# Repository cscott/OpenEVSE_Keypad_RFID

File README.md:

# OpenEVSE Capacitive keypad and RFID reader

Thing tracker at
https://cscott.github.io/thing-tracker/#/thing/c6539aa6-b8c7-4adf-a22c-1baba5bbef97

There is a [Hackaday page for this project].

Discussion in the OpenEVSE forum at
https://openev.freshdesk.com/support/discussions/topics/6000067515

## Description

This repository contains hardware design files for a capacitive
keypad and RFID reader for [OpenEVSE] hardware.

More details can be found on the
[Hackaday page for this project].

<br clear="both" />

## Instructions

### Step 1: Purchase components

You will need to purchase a new
[Polycase ML-58 enclosure](https://www.polycase.com/ml-58f), although
the only part we will need from it is the clear front cover.  (Perhaps
we can arrange a special purchase of just the cover if demand
warrants.)

You will also need to purchase or have the Keypad PCB fabricated.  The
KiCad design files are in the [`Keypad-Front`](./Keypad-Front)
subdirectory. It's a four-layer PCB, and I recommend white silkscreen
to avoid heating when in direct sun.  I used 1oz copper on a standard
1.6mm thick PCB.  I found that [JLCPCB](https://jlcpcb.com/) had
very reasonable prices.

I assume you also own an
[OpenEVSE Advanced Series](https://store.openevse.com/collections/all-products)
and have assembled it.

You will also need an LCD mount, which can be 3d printed.  You *might*
be able to reuse the one from your existing OpenEVSE device, but
you'll need to pry the glue off then cut down the top bar. It's
probably easier just to print a new one.

[`lcd-trim-more.stl`]

For compatibility with the latest OpenEVSE web interface, you will
also need to update the firmware on your main OpenEVSE controller
board.  This is out of scope for this guide, but you can find
instructions HERE.  It's a good thing to do between step 3 and 4
when you have your OpenEVSE charger disconnected and open.

### Step 2: Purchase or fabricate I2C cable

You will also need an I2C cable from the OpenEVSE Wifi board.  If you
have the latest-generation WiFi board, this will be a STEMMA-QT cable
(JST-SH, with 1.0mm pitch).  Older boards had an 8-pin JST-PH
connector (2.0mm pitch) and you will have to fabricate an adapter
yourself.

TODO: photos here

### Step 3: Remove cover from OpenEVSE

Unplug your OpenEVSE.  Don't try to do this with your OpenEVSE still
connected to mains power!

Remove the old printed blue cover from your OpenEVSE.  Disconnect
the cable leading from the OpenEVSE main board to the LCD display.

TODO: photo here.

### Step 4: Move the LCD module

Unscrew the LCD module from your old device and screw it onto the new
LCD mount.  You will then need to attach the new LCD mount to the
Keypad PCB, using the silkscreen as a guide.  I found that hot glue
worked well, but other adhesives are probably fine as well.

TODO: photo here

### Step 5: Mount the new PCB

You will now attach the Keypad PCB to the inside of your new clear
ML-58 enclosure cover.  I found that placing the board inside
the cover and then using generous drops of hot glue around the
screw bosses secured the Keypad PCB in a reversible manner, so that I
could still remove it if I needed to later.

TODO: photo here

If you're braver, a clear contact-sensitive adhesive tape (3M
makes a number of different types) would make a more permanent
bond.  Eliminating the air gap between the front cover and the
Keypad PCB is said to yield better performance from capacitive touch
sensors, but the hot-glue method has worked well enough for me.

### Step 5: Connect cables

You will need to connect two cables:

1. The LCD cable that you removed in step 3.

TODO: photo here

2. The I2C cable from step 2, from the OpenEVSE Wifi board to the
STEMMA-QT-compatible ports on the Keypad PCB.

TODO: photo here

### Step 6: Reattach the cover

Screw the cover back on the OpenEVSE!

TODO: photo here

### Step 7: Update OpenEVSE firmware

You'll need to reflash the OpenEVSE to the latest firmware.  The
good news is that you can do this over the web interface!

TODO: instructions here

### Step 8: Add some PINs and cards

TODO: instructions here

### Step 9: Optional improvements

The Keypad PCB also contains an MCP9808 temperature sensor and pads
for a DS3231MZ real-time clock.  Some older versions of the OpenEVSE
hardware contained an MCP9808 daisy-chained from the LCD module and
secured to the front cover.  If your hardware is like this, then
you can use the MCP9808 on the board by connecting the LCD display
to this port on the keypad PCB:

TODO: photo here

You should be able to use your existing cable, but if you have to
purchase or fabricate a new one, it's a STEMMA-QT compatible JST-SH
(1.0mm pitch) on the Keypad PCB side.  On my example, it was JST-PH
(2.0mm pitch) on the LCD side, and you can [buy an appropriate cable
from Adafruit](https://www.adafruit.com/product/4424).

Similarly, *newer* versions of the OpenEVSE hardware omit the
real-time clock which was present on the original OpenEVSE LCD modules.
The justification is that, with ubiquitous network connectivity,
you don't need to pay the steep price (~$10) for a clock chip when
instead you can just ask the network what time it is.

However, if you have intermittent network connectivity at your
installation site, you might want the peace of mind of knowing that
your usage timestamps will always be correct.  Because the RTC chip
is not cheap, it is not populated on the keypad PCB by default,
although all of its support components are present.  You can buy
an appropriate chip ([Digikey part link](https://www.digikey.com/en/products/detail/analog-devices-inc-maxim-integrated/DS3231MZ/2754396))
and battery connector ([Digikey part link](https://www.digikey.com/en/products/detail/mpd-memory-protection-devices/BC-2003-TR/5027929))
and hand-solder them onto the footprints provided.  While you've got
the soldering iron hot, you will most likely want to *remove* the
MCP9808 chip present on the Keypad PCB, since as far as I'm aware
all of the LCD modules *missing* the RTC *also* have the MCP9808
already present on the LCD board.  You don't want two MCP9808s trying
to talk on the same I2C bus.

After adding the RTC, you'd connect the I2C cable from the LCD
module to the Keypad PCB just as done for the MCP9808 above.

## Related

* [OpenEVSE] project
* [Hackaday page for this project]

## License

These designs are licensed under the [CC-BY-SA-4.0] like the original
OpenEVSE designs.

[OpenEVSE]: https://www.openevse.com/
[Hackaday page for this project]: https://hackaday.io/project/194656-openevse-capacitive-keypad-rfid
[`lcd-trim-more.stl`]: ./lcd-trim-more.stl
[CC-BY-SA-4.0]: https://spdx.org/licenses/CC-BY-SA-4.0.html

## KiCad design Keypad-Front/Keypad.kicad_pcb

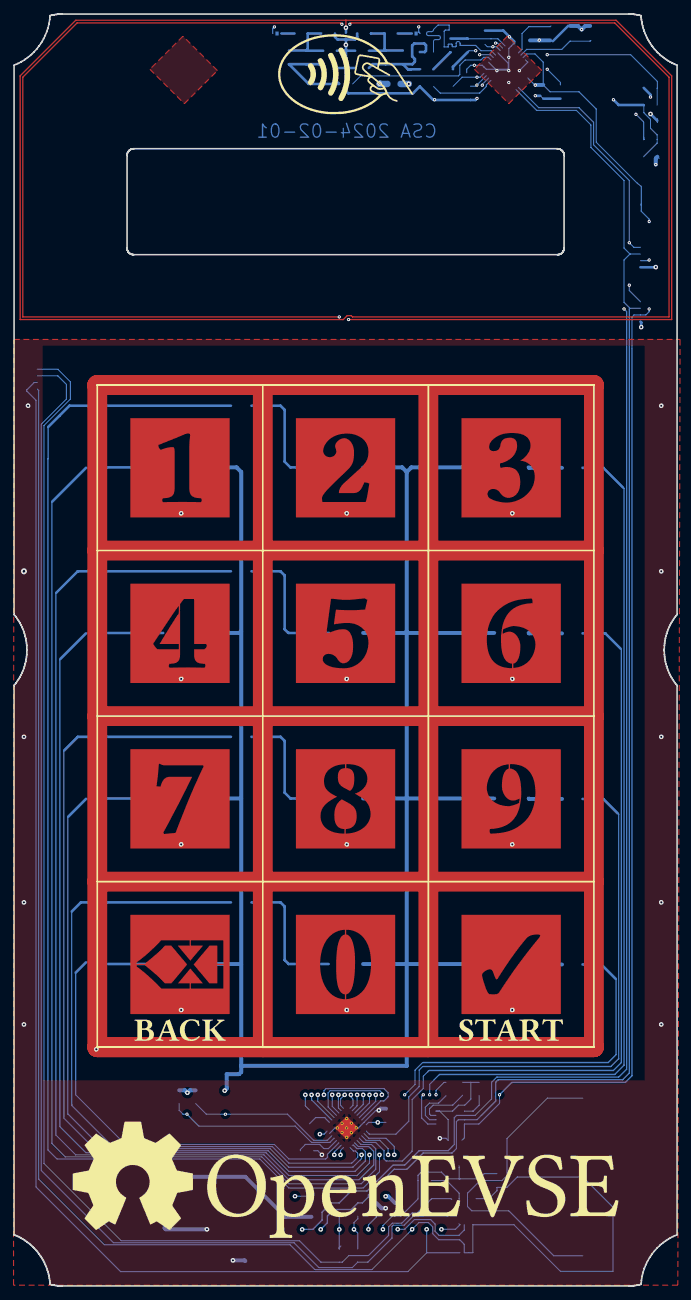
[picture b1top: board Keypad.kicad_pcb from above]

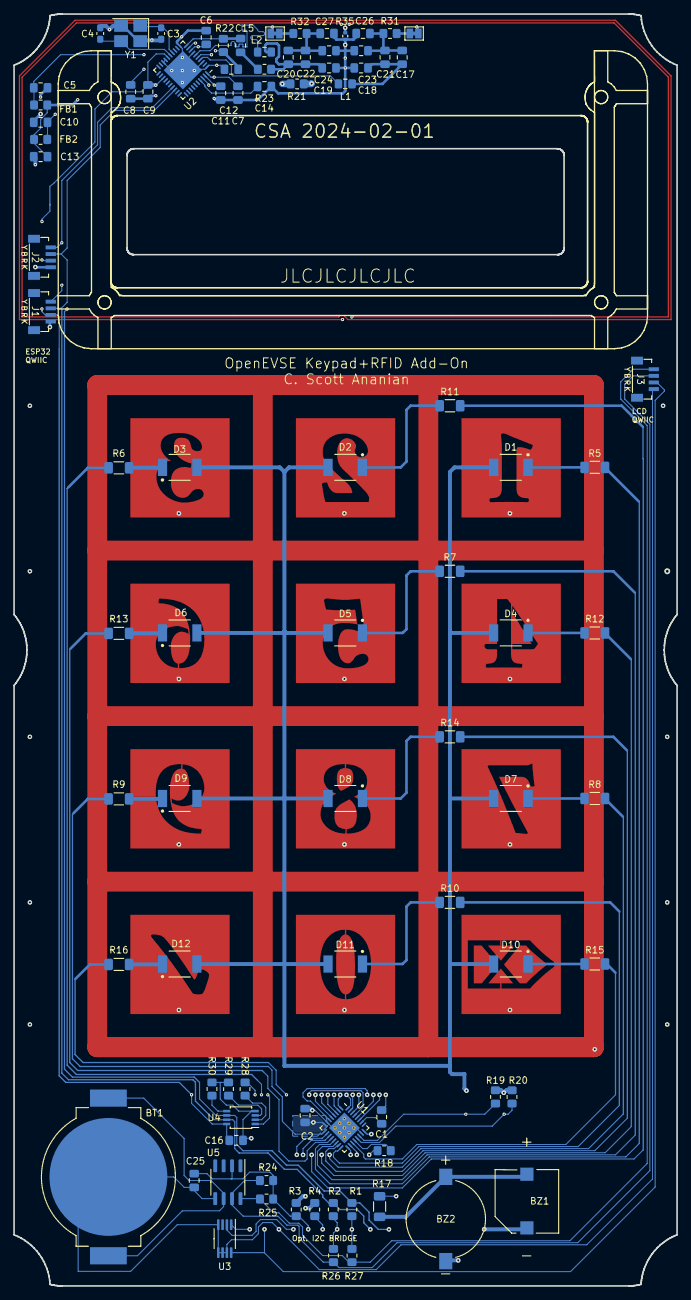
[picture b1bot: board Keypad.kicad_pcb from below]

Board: 4 copper layers, 100.1 x 192.1 mm, 103 parts (90 on the bottom side), 74 nets.

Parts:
BT1: CR2032; BatteryHolder_MPD_BC2003_1x2032
BZ1: FUET-9650B-3V
BZ2: PUI SMT-1220-TW-R; XDCR_SMT-1220-TW-R
C1: 47pF; C_0805_2012Metric_Pad1.18x1.45mm_HandSolder
C2, C6, C7, C8, C9, C11, C12, C13, C16, C25: .1uF; C_0805_2012Metric_Pad1.18x1.45mm_HandSolder
C3, C4: 33pF; C_0603_1608Metric_Pad1.08x0.95mm_HandSolder
C5, C10, C14: 10uF; C_0805_2012Metric_Pad1.18x1.45mm_HandSolder
C15: 1000pF; C_0805_2012Metric_Pad1.18x1.45mm_HandSolder
C17, C20, C26, C27: N/C; C_0805_2012Metric_Pad1.18x1.45mm_HandSolder
C18, C19: 220pF; C_0805_2012Metric_Pad1.18x1.45mm_HandSolder
C21, C22: 22pF; C_0805_2012Metric_Pad1.18x1.45mm_HandSolder
C23, C24: 100pF; C_0805_2012Metric_Pad1.18x1.45mm_HandSolder
D1, D2, D3, D4, D5, D6, D7, D8, D9, D10, D11, D12: SunLED XZVG45WT-9; SunLED_3.2x2.8mm_ReverseMount
FB1, FB2: Laird MI0805J102R-10; R_0805_2012Metric_Pad1.20x1.40mm_HandSolder
J1: EXP QWIIC; JST-SH-4-VERT-SMD
J2: TOUCH QWIIC; JST-SH-4-VERT-SMD
J3: RTC STEMMA QT; JST-SH-4-VERT-SMD
L1, L2: 560nH; L_0805_2012Metric_Pad1.15x1.40mm_HandSolder
R1, R2, R3, R4, R26, R27: 0; R_0805_2012Metric_Pad1.20x1.40mm_HandSolder
R5, R6, R7, R8, R9, R10, R11, R12, R13, R14, R15, R16, R17: 100; R_1206_3216Metric_Pad1.30x1.75mm_HandSolder
R18, R24, R25: 4.7k; R_0805_2012Metric_Pad1.20x1.40mm_HandSolder
R19, R20, R21: 10k; R_0805_2012Metric_Pad1.20x1.40mm_HandSolder
R22, R28, R29, R30: 1k; R_0805_2012Metric_Pad1.20x1.40mm_HandSolder
R23: 2.7k; R_0805_2012Metric_Pad1.20x1.40mm_HandSolder
R31, R32: 1.5; R_0805_2012Metric_Pad1.20x1.40mm_HandSolder
R33, R34: N/C; SolderJumper-2_P1.3mm_Bridged_Pad1.0x1.5mm
R35: 0; R_0402_1005Metric
TP1: Guard; Touch_Pad_D1.0mm
TP2: KEY 4; Touch_Pad_D1.0mm
TP3: KEY 7; Touch_Pad_D1.0mm
TP4: KEY 6; Touch_Pad_D1.0mm
TP5: KEY 1; Touch_Pad_D1.0mm
TP6: KEY 5; Touch_Pad_D1.0mm
TP7: KEY 8; Touch_Pad_D1.0mm
TP8: KEY 0; Touch_Pad_D1.0mm
TP9: KEY 2; Touch_Pad_D1.0mm
TP10: KEY 3; Touch_Pad_D1.0mm
TP11: KEY ENTER; Touch_Pad_D1.0mm
TP12: KEY 9; Touch_Pad_D1.0mm
TP13: KEY BACK; Touch_Pad_D1.0mm
U1: CAP1214; QFN-32-1EP_5x5mm_P0.5mm_EP3.3x3.3mm_ThermalVias
U2: PN5321A3HN_C1xx; HVQFN-40-1EP_6x6mm_P0.5mm_EP4.1x4.1mm
U3: MCP9808_MSOP; MSOP-8_3x3mm_P0.65mm
U4: PCA9536DP; TSSOP-8_3x3mm_P0.65mm
U5: DS3231MZ; SOIC-8_3.9x4.9mm_P1.27mm
Y1: 27.12MHz; Crystal_SMD_TXC_7M-4Pin_3.2x2.5mm_HandSoldering

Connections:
+3.3V: C2.1, C7.1, C9.1, C16.1, D1.2 (A), D2.2 (A), D3.2 (A), D4.2 (A), D5.2 (A), D6.2 (A), D7.2 (A), D8.2 (A), D9.2 (A), D10.2 (A), D11.2 (A), D12.2 (A), J1.2, J2.2, R3.1, R19.1, R20.1, R21.1, R28.2, U1.8 (VDD), U2.16 (I0), U2.23 (PVDD), U2.40 (VBAT), U4.8 (VDD)
+5V: C25.1, J3.2, R3.2, R24.1, R25.1, U3.8 (V_{DD}), U5.2 (VCC)
/FEEDBACK: BZ1.1 (+), BZ2.1 (+), R17.1
/FEED_N: C19.2, C20.1, C22.1, L2.2, R23.1
/FEED_P: C17.2, C18.1, C21.2, L1.2
/LED1: R5.1, U1.13 (LED5)
/LED2: R11.1, U1.17 (LED9)
/LED3: R6.1, U1.18 (LED10)
/LED4: R12.1, U1.10 (LED2)
/LED5: R7.1, U1.14 (LED6)
/LED6: R13.1, U1.12 (LED4)
/LED7: R8.1, U1.11 (LED3)
/LED8: R14.1, U1.15 (LED7)
/LED9: R9.1, U1.9 (LED1)
/LED10: R15.1, U1.19 (LED11)
/LED11: R10.1, U1.16 (LED8)
/LED12: R16.1, U4.1 (IO0)
/RTC_SCL: J3.4, R25.2, R27.1, U5.8 (SCL)
/RTC_SDA: J3.3, R24.2, R26.1, U5.7 (SDA)
/TEMP_SCL: R1.2, R27.2, U3.2 (SCL)
/TEMP_SDA: R2.2, R26.2, U3.1 (SDA)
/TOUCH_1: TP5.1, U1.30 (CS5)
/TOUCH_2: TP9.1, U1.2 (CS9)
/TOUCH_3: TP10.1, U1.3 (CS10)
/TOUCH_4: TP2.1, U1.27 (CS2)
/TOUCH_5: TP6.1, U1.31 (CS6)
/TOUCH_6: TP4.1, U1.29 (CS4)
/TOUCH_7: TP3.1, U1.28 (CS3)
/TOUCH_8: TP7.1, U1.32 (CS7)
/TOUCH_9: TP12.1, U1.5 (CS12)
/TOUCH_10: TP13.1, U1.6 (CS13)
/TOUCH_11: TP8.1, U1.1 (CS8)
/TOUCH_12: TP11.1, U1.4 (CS11)
/TOUCH_GUARD: C1.1, TP1.1
/TOUCH_SCL: J1.4, J2.4, R1.1, R19.2, U1.22 (SMCLK), U2.27 (NSS/P50_SCL/HSU_RX), U4.6 (SCL)
/TOUCH_SDA: J1.3, J2.3, R2.1, R20.2, U1.21 (SMDATA), U2.28 (MOSI/SDA/HSU_TX), U4.7 (SDA)
/TX_N: L2.1, U2.6 (TX2)
/TX_P: L1.1, U2.4 (TX1)
GND1: BZ1.2 (-), BZ2.2 (-), C2.2, C3.1, C4.1, C5.2, C6.1, C7.2, C8.1, C9.2, C10.2, C11.2, C12.2, C13.1, C14.2, C16.2, C18.2, C19.1, C23.2, C24.1, C26.2, C27.1, J1.1, J2.1, R4.1, R18.2, R29.2, R30.2, R35.1, U1.7 (CS14), U1.23 (RESET), U1.33 (GND), U2.1 (DVSS), U2.3 (TVSS1), U2.7 (TVSS2), U2.11 (AVSS), U2.17 (I1), U2.18 (TESTEN), U2.41 (AVSS), U4.4 (VSS), Y1.2, Y1.4
GND2: BT1.2 (-), C25.2, J3.1, R4.2, U3.4 (GND), U3.5 (A2), U3.6 (A1), U3.7 (A0), U5.5 (GND)
unnamed: BT1.1 (+), U5.6 (VBAT)
unnamed: C15.2, R23.2
unnamed: C17.1, C21.1, C23.1, C26.1, R31.2
unnamed: C20.2, C22.2, C24.2, C27.2, R32.1
unnamed: D1.1 (K), R5.2
unnamed: D2.1 (K), R11.2
unnamed: D3.1 (K), R6.2
unnamed: D4.1 (K), R12.2
unnamed: D5.1 (K), R7.2
unnamed: D6.1 (K), R13.2
unnamed: D7.1 (K), R8.2
unnamed: D8.1 (K), R14.2
unnamed: D9.1 (K), R9.2
unnamed: D10.1 (K), R15.2
unnamed: D11.1 (K), R10.2
unnamed: D12.1 (K), R16.2
unnamed: R31.1, R33.2
unnamed: R32.2, R34.1
unnamed: R33.1, R34.2, R35.2
unnamed: R18.1, U1.20 (ALERT)
unnamed: C1.2, U1.26 (CS1)
unnamed: R17.2, U1.24 (FEEDBACK)
unnamed: C5.1, C6.2, FB1.2, U2.8 (AVDD)
unnamed: C3.2, U2.14 (OSCIN), Y1.1
unnamed: C4.2, U2.15 (OSCOUT), Y1.3
unnamed: C15.1, R22.2, U2.10 (RX)
unnamed: C14.1, U2.37 (SVDD)
unnamed: C8.2, C10.1, FB2.2, U2.5 (TVDD)
unnamed: C12.1, R22.1, U2.9 (VMID)
unnamed: R21.2, U2.38 (~RSTPD)
unnamed: R28.1, U4.2 (IO1)
unnamed: R29.1, U4.3 (IO2)
unnamed: R30.1, U4.5 (IO3)
VCC: C11.1, C13.2, FB1.1, FB2.1, U2.39 (DVDD)

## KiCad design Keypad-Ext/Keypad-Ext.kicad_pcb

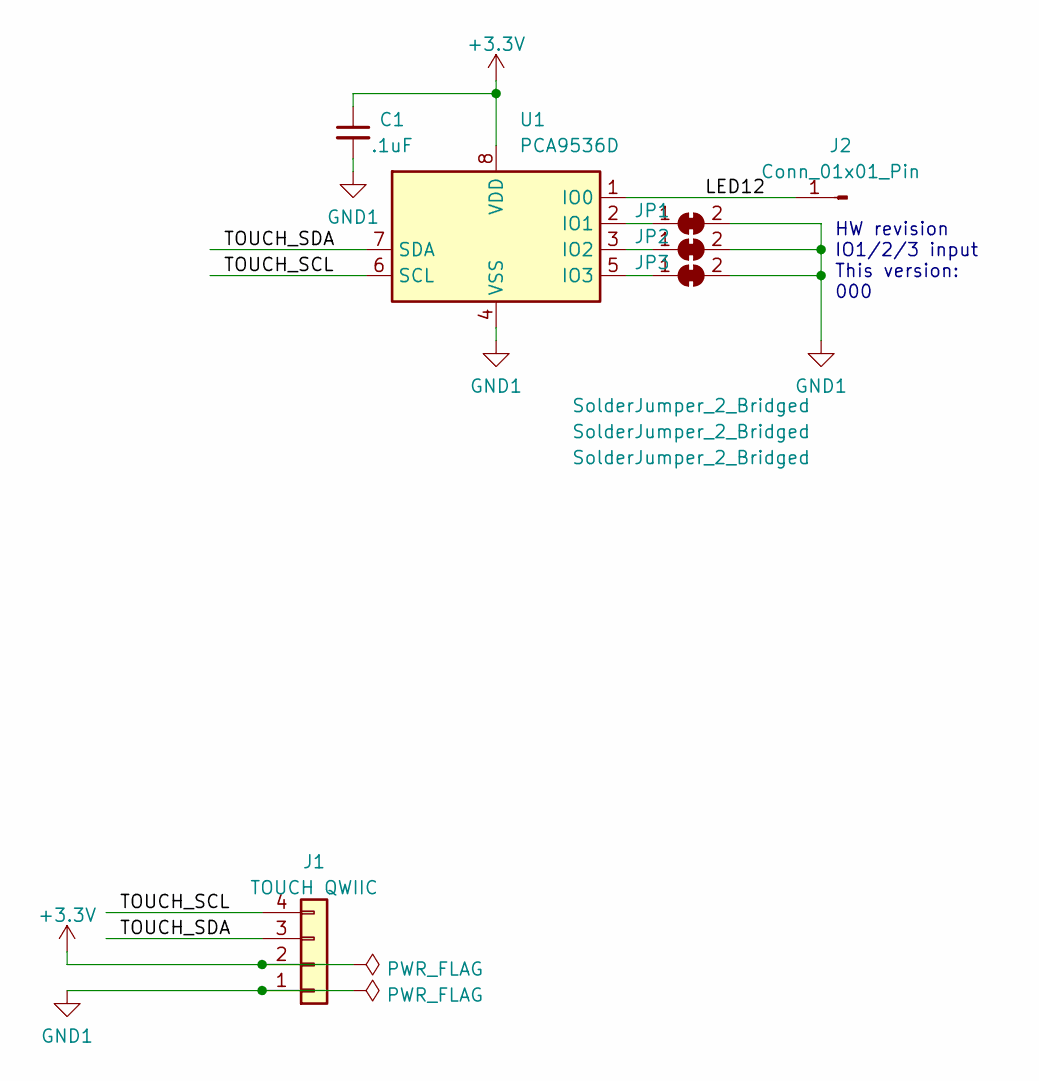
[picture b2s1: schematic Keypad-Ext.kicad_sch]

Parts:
C1: .1uF; C_0805_2012Metric_Pad1.18x1.45mm_HandSolder; LCSC C138340
J1: TOUCH QWIIC; JST-SH-4-VERT-SMD; LCSC C160390
J2: Conn_01x01_Pin; PinHeader_1x01_P2.54mm_Vertical
JP1, JP2, JP3: SolderJumper_2_Bridged; SolderJumper-2_P1.3mm_Bridged_Pad1.0x1.5mm
U1: PCA9536D; SOIC-8_3.9x4.9mm_P1.27mm; LCSC C2688883

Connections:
+3.3V: C1.1, J1.2, U1.8 (VDD)
/LED12: J2.1, U1.1 (IO0)
/TOUCH_SCL: J1.4, U1.6 (SCL)
/TOUCH_SDA: J1.3, U1.7 (SDA)
GND1: C1.2, J1.1, JP1.2 (B), JP2.2 (B), JP3.2 (B), U1.4 (VSS)
unnamed: JP1.1 (A), U1.2 (IO1)
unnamed: JP2.1 (A), U1.3 (IO2)
unnamed: JP3.1 (A), U1.5 (IO3)

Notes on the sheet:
HW revision IO1/2/3 input This version: 000

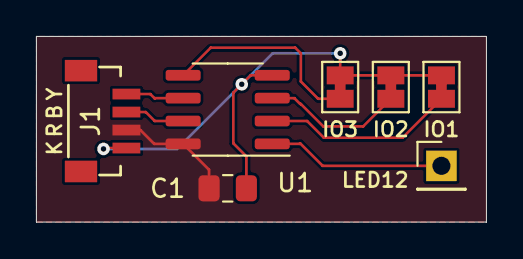
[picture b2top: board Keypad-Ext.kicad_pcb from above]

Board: 2 copper layers, 25.0 x 10.3 mm, 7 parts (0 on the bottom side), 8 nets.

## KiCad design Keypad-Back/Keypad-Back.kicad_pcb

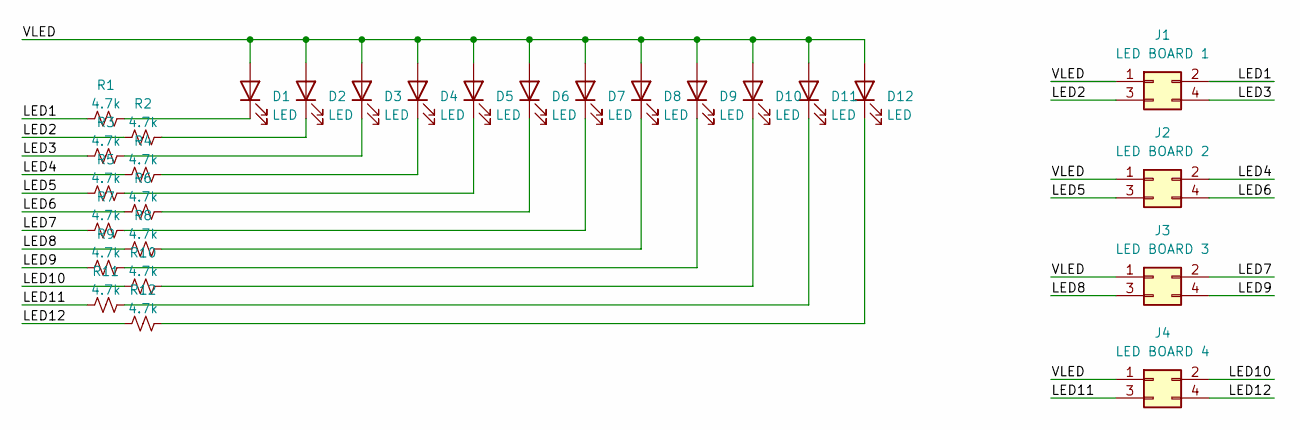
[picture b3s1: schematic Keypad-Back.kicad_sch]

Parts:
D1, D2, D3, D4, D5, D6, D7, D8, D9, D10, D11, D12: LED; LED_1206_3216Metric_Pad1.42x1.75mm_HandSolder
J1: LED BOARD 1; PinHeader_2x02_P2.54mm_Vertical_SMD
J2: LED BOARD 2; PinHeader_2x02_P2.54mm_Vertical_SMD
J3: LED BOARD 3; PinHeader_2x02_P2.54mm_Vertical_SMD
J4: LED BOARD 4; PinHeader_2x02_P2.54mm_Vertical_SMD
R1, R2, R3, R4, R5, R6, R7, R8, R9, R10, R11, R12: 4.7k; R_0805_2012Metric_Pad1.20x1.40mm_HandSolder

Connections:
/LED1: J1.2, R1.1
/LED2: J1.3, R2.1
/LED3: J1.4, R3.1
/LED4: J2.2, R4.1
/LED5: J2.3, R5.1
/LED6: J2.4, R6.1
/LED7: J3.2, R7.1
/LED8: J3.3, R8.1
/LED9: J3.4, R9.1
/LED10: J4.2, R10.1
/LED11: J4.3, R11.1
/LED12: J4.4, R12.1
/VLED: D1.2 (A), D2.2 (A), D3.2 (A), D4.2 (A), D5.2 (A), D6.2 (A), D7.2 (A), D8.2 (A), D9.2 (A), D10.2 (A), D11.2 (A), D12.2 (A), J1.1, J2.1, J3.1, J4.1
unnamed: D1.1 (K), R1.2
unnamed: D2.1 (K), R2.2
unnamed: D3.1 (K), R3.2
unnamed: D4.1 (K), R4.2
unnamed: D5.1 (K), R5.2
unnamed: D6.1 (K), R6.2
unnamed: D7.1 (K), R7.2
unnamed: D8.1 (K), R8.2
unnamed: D9.1 (K), R9.2
unnamed: D10.1 (K), R10.2
unnamed: D11.1 (K), R11.2
unnamed: D12.1 (K), R12.2

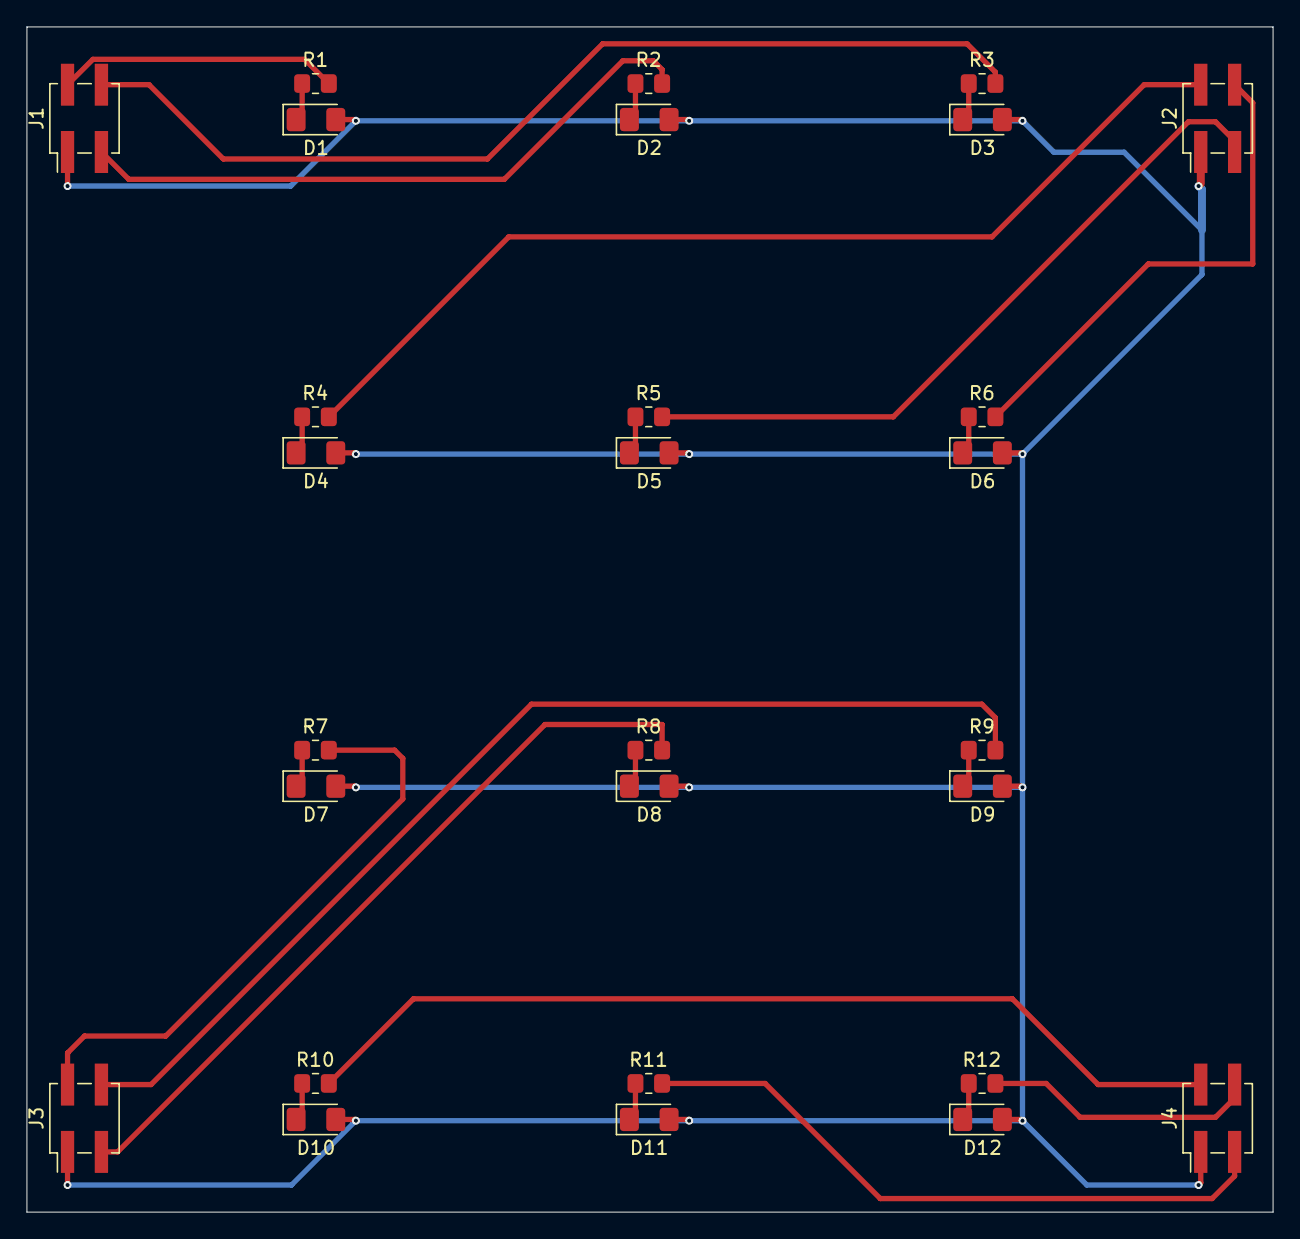
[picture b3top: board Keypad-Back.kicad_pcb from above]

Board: 2 copper layers, 93.5 x 88.9 mm, 28 parts (0 on the bottom side), 25 nets.

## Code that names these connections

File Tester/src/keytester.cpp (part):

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    cap1214_write(CAP1214_REG_SENSOR_LED_LINKING, 0x76);
  }
  // LED/GPIO pins are outputs!
  cap1214_write(CAP1214_REG_LED_GPIO_DIRECTION, 0xFF); // LED1-LED8 = output
  // flip polarity of all LEDs (normally off, to keep power low)
  polarity = POLARITY_ASLEEP;
  cap1214_write(CAP1214_REG_LED_POLARITY_1, polarity);
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  if (st3 & 0xF) { merged |= 0x80; }

#define merged_cs(x) (merged & (((uint16_t)1)<<(x-1)))
  // manually set feedback pins for CS8-CS13
  // CS8/9/10 -> LED8/9/10
  uint8_t led1 = 0, led2 = 0, led3 = 0;
  static bool saw_cs8 = false;
  if (merged_cs(8)) { // CS8 (touch 11, key 0)
    led1 |= 0x80;
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
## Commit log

2023-07-04 Initial version of OpenEVSE keypad
2023-07-04 Reorg into separate front and back PCB
    This would allow the use of "normal" front-view LEDs, ie UV LEDs
    to exploit the "natural" flourescence of FR4.
2023-07-05 Back to a one-board design with rear-firing LEDs
    Giving up on the UV LED idea for now.
2023-07-05 Steady work on Keypad PCB
2023-07-06 Attempt 2 at routing, cap sensor at bottom
2023-07-07 Take 3, the JST-XH for the feedback is too large.
2023-07-08 Complete!
2023-07-08 First version of gerbers
2023-07-09 Second version, to fix the disconnected touch pad centers
    Tried to get JLCPCB to adopt this, but apparently unsuccessfully.
2023-07-10 Third version, no vias to cast shadows.
    Also add the BOM.
2023-09-04 Keypad tester skeleton
2023-09-06 Fix schematic and PCB
    1. Swap LED6 and LED11 so that the dual LED is on the high-power port.
    (This change isn't green-wired on the existing boards.)
    2. Add 47pF series cap to TOUCH_GUARD to bring it into spec.
    (Measured at 80pF; CAP1214 supports 50pF max.)
    3. Fix RESET -- it should be grounded, not tied high.
2023-09-06 First complete key tester
2023-09-06 Tweak sensitivity and other values
2023-09-06 More tweaks & testing of proximity feature
2023-09-06 Improve key press responsiveness
2023-09-07 Fix handling of zero key (CS8) which has a weird press-and-hold feature
2023-09-07 Increase prox sensitivity
2023-09-25 Fix some errors in original boards; add RFID functionality
2023-10-21 Resync cap1214 code with upstream
2023-10-21 CAP1214 updates for hardware v2
2023-10-21 Add support for testing MCP9808
2023-10-21 Relocate traces for keypad 2/5/8 which got moved somehow
2023-10-21 Add PN532 tester
2023-10-23 Ensure that all CAP1214 sensors are turned on
2023-10-24 Add PCA9536 I/O expander to handle LED12 and hardware version detect
2023-10-25 Simplify schematic and PCB
    Remove the solder jumper for SEL0/SEL1, that's been tested & is correct.
    Add 0-ohm resistors for GPIO expander to accomodate future green wire hacks.
    Mark the DNP components on the schematic.
2023-10-25 Clean up merged_cs #define
2023-11-04 Add support for PCA9536 and automatic detection of HW_V2
2023-11-04 PCA9536 polarity only controls *input* not *output*
2024-01-31 Add some .gitignored files to Keypad-Back
    I don't think these are actually necessary, but I'm about to delete
    this subdirectory in the next commit so I figured I'd stick them in
    the repo just in case.
2024-01-31 Remove "Keypad Back"
    This directory was left over from "revision 0" of the design, when
    the forward-shining UV LEDs were mounted on a separate PCB separated
    from the main board with 4-pin headers.
2024-01-31 Add Keypad-Ext
    This was a temporary bodge board for the Revision 2 hardware, which added
    a PCA9536 I/O expander to allow LED12 to be driven separately. Also
    the presence of PCA9536 on the I2C bus was also an indicator we were
    running on "revision 2" hardware, which had some of the capacitive
    sense lines moved around compare to revision 1 hardware.
    In the end I didn't end up using these files; I redrew the schematic
2024-02-01 Remove Keypad-Ext bodge board -- unnecessary for Revision 3 hardware
2024-02-01 More schematic cleanup
    * Remove silkscreen for R23/R24, which are shorted jumpers as a netlist
    hack for the PCB antenna, not "real" components.
    * Remove unnecessary R15 (and its traces) now that we have PCA9536 to
    drive LED12.
2024-02-01 Add schematic PDF for easy browsing
2024-02-01 Add README and thing.json
2024-02-01 More work on schematic and gerbers; fill out BOM with JLCPCB part #s
    Also updated the README a bit.
2024-02-01 Add STL for LCD mount
2024-02-02 RFID tuning
    Tuned the length of the TX1 and TX2 traces to maintain symmetry; moved
    L1/L2 around a bit to the same end. Added a zero-ohm resistor so we
    can disconnect the antenna "virtual ground" from the actual ground,
    as recommended by the AN1445 app note.
2024-02-02 README: link all the things
2024-02-03 Add missing LCD mount stl files
